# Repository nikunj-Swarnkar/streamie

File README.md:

### streamie

---

a hackpad or a streaming device with a gamepad in which you can stream your games or play some retro games natively , hack it , add a keyboard and sky is your limit , it runs android !

---

## Cad 

this is the case i prepared 

## PCB

---

## Flashing
for the Raxda please follow raxda offical guide , please flash it before assembly 
[Raxda Site](https://docs.radxa.com/en/cubie/a7z/other-system/android)

The controller runs on an RP2040-Zero and flashes by drag-and-drop. No programmer is needed.

### Option 1: flash a prebuilt file
1. Download `controller_xinput.uf2` from the Releases page.
2. Unplug the board from USB.
3. Hold the **BOOT** button and plug the board into your computer. Release BOOT once it's connected.
4. A drive named **RPI-RP2** appears. Drag `controller_xinput.uf2` onto it.
5. The drive disappears and the board restarts as a controller.

### Option 2: build it yourself
Requirements: [VS Code](https://code.visualstudio.com/) with the **Raspberry Pi Pico** extension. It installs the Pico SDK (2.x), compiler and CMake for you.

1. Clone this repo and open the `firmware/xinput` folder in VS Code (**File > Open Folder**). It must be the folder that directly contains `CMakeLists.txt`.
2. In the Pico extension, choose **Import Project** and select that folder.
3. Check that `CMakeLists.txt` has `set(PICO_BOARD waveshare_rp2040_zero)`. Use `pico` if you have a regular Raspberry Pi Pico.
4. Click **Compile Project**. The result is `build/controller_xinput.uf2`.
5. Flash it with the steps from Option 1.

If you use the command line instead, run:
```
mkdir build && cd build
cmake -DPICO_SDK_PATH=/path/to/pico-sdk ..
cmake --build .
```

### Verify it works
1. Keep the **sticks centered and the triggers released** when you plug it in, because they are calibrated at power-up.
2. On Windows, press **Win + R**, type `joy.cpl` and press Enter. The board should appear as **Xbox 360 Controller**.
3. Open **Properties** and check every button, both sticks and both triggers.
4. Pull each trigger fully once so it learns its travel.

### Settings in `main.c`
| Setting | What it does |
|---|---|
| `INVERT_LY`, `INVERT_RY` | Set to `true` if a stick's up and down are backwards |
| `STICK_DEADZONE` | Raise it if the sticks drift |
| `R3_PRESSED_BELOW` | Threshold for the right stick click, which is read through the MCP3008 (CH6) |

### Updating the firmware
Repeat the flashing steps. Always hold **BOOT** while plugging in, even if the board is already running this firmware.

### Troubleshooting
- **No RPI-RP2 drive:** try a different USB cable, because many cables carry power only. Make sure you hold BOOT *before* plugging in.
- **Not recognised as an Xbox controller:** check Device Manager for an unknown device, and try a different USB port.
- **Triggers read constant or backwards:** check the trigger pot wiring. The wiper (middle pad) must go to the MCP3008 channel.
- **Stick axes backwards:** flip `INVERT_LY` or `INVERT_RY` and re-flash.
- **No rumble:** it works only in games and testers that send XInput rumble. Check that the motor MOSFET gates are wired to GP26 and GP27.
- **Compile fails in VS Code:** make sure the open folder is the one containing `CMakeLists.txt`, then run **Clean CMake** and **Compile Project** again.

Compatibility: Windows and Linux. Consoles will not accept this controller.

---

## Assembly 

after printing the case add screen on in it 

then add the front latch to the screen and secure it with 4 M3 screws 

after that add all the buttons from the back 

then put the pcb on it 

and then rest of the parts and add aux post connected to the screen and add a A7z with stand off and wire everything 

connect the controller through usb cable after connecting both side with jst connector , then wire the tp4056 with buck convertor and make sure to set it at 5 v 

after that add the battery to the back and stick it to the back indent with m3 tape or doulbe side tape

after that then just wire it to the tp4056 
and the buckconvertor to the 5v n gnd of the Raxda A7z connect the display with hdmi and if u want touch a usb cable 

after all that 

just screw in the last 4 M3 screws 

and we are done ! 

---

# Bill of Materials (BOM)

| Sr. No. | Name | Link | Unit Price (USD) | Quantity | Total Price (USD) |
|---:|---|---|---:|---:|---:|
| 1 | JST male | [Product link](https://sharvielectronics.com/product/ph-14aw-14-pin-jst-right-angle-male-connector-2mm-pitch/) | 0.130 | 6 | 0.780 |
| 2 | JST female | [Product link](https://sharvielectronics.com/product/jst-ph-14-14-pin-single-side-female-to-free-end-connector-with-2mm-pitch-30cm-wire-length/) | 0.510 | 6 | 3.060 |
| 3 | 90-degree push button | [Product link](https://sharvielectronics.com/product/push-button-right-angle-tactile-switch-6x5mm-right-angle-tactile-switch-momentary-switch/) | 0.710 | 10 | 7.100 |
| 4 | Joystick | [Product link](https://sharvielectronics.com/product/thumb-joystick-switch-xy-dual-axis-4-way-direction/) | 0.660 | 4 | 2.640 |
| 5 | Screen | [Product link](https://makerbazar.in/products/waveshare-5-inch-capacitive-hdmi-lcd-display-h-800-480?variant=43342621311216) | 51.670 | 1 | 51.670 |
| 6 | Battery | [Product link](https://makerbazar.in/products/single-cell-3-7v-10000mah-lipo-battery?variant=48251044659440) | 4.120 | 1 | 4.120 |
| 7 | Buck converter (listed as XL6009) | [Product link](https://makerbazar.in/products/xl6009-dc-dc-adjustable-boost-buck-step-up-step-down-converter-module) | 0.670 | 1 | 0.670 |
| 8 | SMD push button | [Product link](https://makerbazar.in/products/5-2x5-2mm-smd-copper-push-button-tactile-switch?variant=48101517852912) | 0.200 | 2 | 0.400 |
| 9 | Vibration motor | [Product link](https://makerbazar.in/products/coin-type-micro-disc-vibration-motor?variant=48251066024176) | 0.200 | 4 | 0.800 |
| 10 | MCP3008 ADC | [Product link](https://sharvielectronics.com/product/mcp3008-i-p-8-channel-10-bit-adc-with-spi-interface-ic-dip-16-package/) | 3.530 | 1 | 3.530 |
| 11 | 1N4739A Zener diode (9.1 V) | [Product link](https://sharvielectronics.com/product/1n4739a-9-1v-1watt-zener-diode-%c2%b15-tolerance-do-41-package/) | 0.034 | 4 | 0.136 |
| 12 | Waveshare RP2040 Zero | [Product link](https://sharvielectronics.com/product/waveshare-rp2040-zero-without-header/) | 3.800 | 1 | 3.800 |
| 13 | AO3400 MOSFET | [Product link](https://sharvielectronics.com/product/ao3400-30v-5-8a-n-channel-mosfet-sot-23-package/) | 0.100 | 5 | 0.500 |
| 14 | RK09K1110A0J | [Product link](https://robu.in/product/1-month-warranty-1035/) | 0.580 | 2 | 1.160 |
| 15 | 10 kΩ resistor | [Product link](https://sharvielectronics.com/product/10k-ohm-1-watt-metal-film-resistor-1-tolerance/) | 0.920 | 10 | 9.200 |
| 16 | 100 Ω resistor | [Product link](https://sharvielectronics.com/product/100-ohm-1-2-watt-resistor-5-tolerance/) | 0.012 | 10 | 0.120 |
| 17 | 100 kΩ resistor | [Product link](https://sharvielectronics.com/product/100k-ohm-2-watt-metal-film-resistor-1-tolerance/) | 0.095 | 10 | 0.950 |
| 18 | Radxa Cubie A7Z | [Product link](https://evelta.com/cubie-a7z-tiny-size-mighty-ai-sbc-radxa/) | 62.120 | 1 | 62.120 |
| 19 | AUX port/cable | [Product link](https://sharvielectronics.com/product/3-5mm-aux-male-to-female-audio-extension-cable-1-meter/) | 1.020 | 1 | 1.020 |
| 20 | Micro-HDMI to HDMI cable/adapter | [Product link](https://sharvielectronics.com/product/micro-hdmi-male-to-hdmi-male-adapter/) | 1.540 | 1 | 1.540 |
| 21 | USB-C to USB-C cable | [Product link](https://www.amazon.in/Wayona-Powerbank-charging-compatible-Samsung/dp/B08WKJN4LF?source=ps-sl-shoppingads-lpcontext&smid=A2V43CXDBM3YTI&th=1) | 3.030 | 1 | 3.030 |
|  | **Grand Total** |  |  |  | **158.346** |

---

and we are done , ill update the github now when i make the project ~

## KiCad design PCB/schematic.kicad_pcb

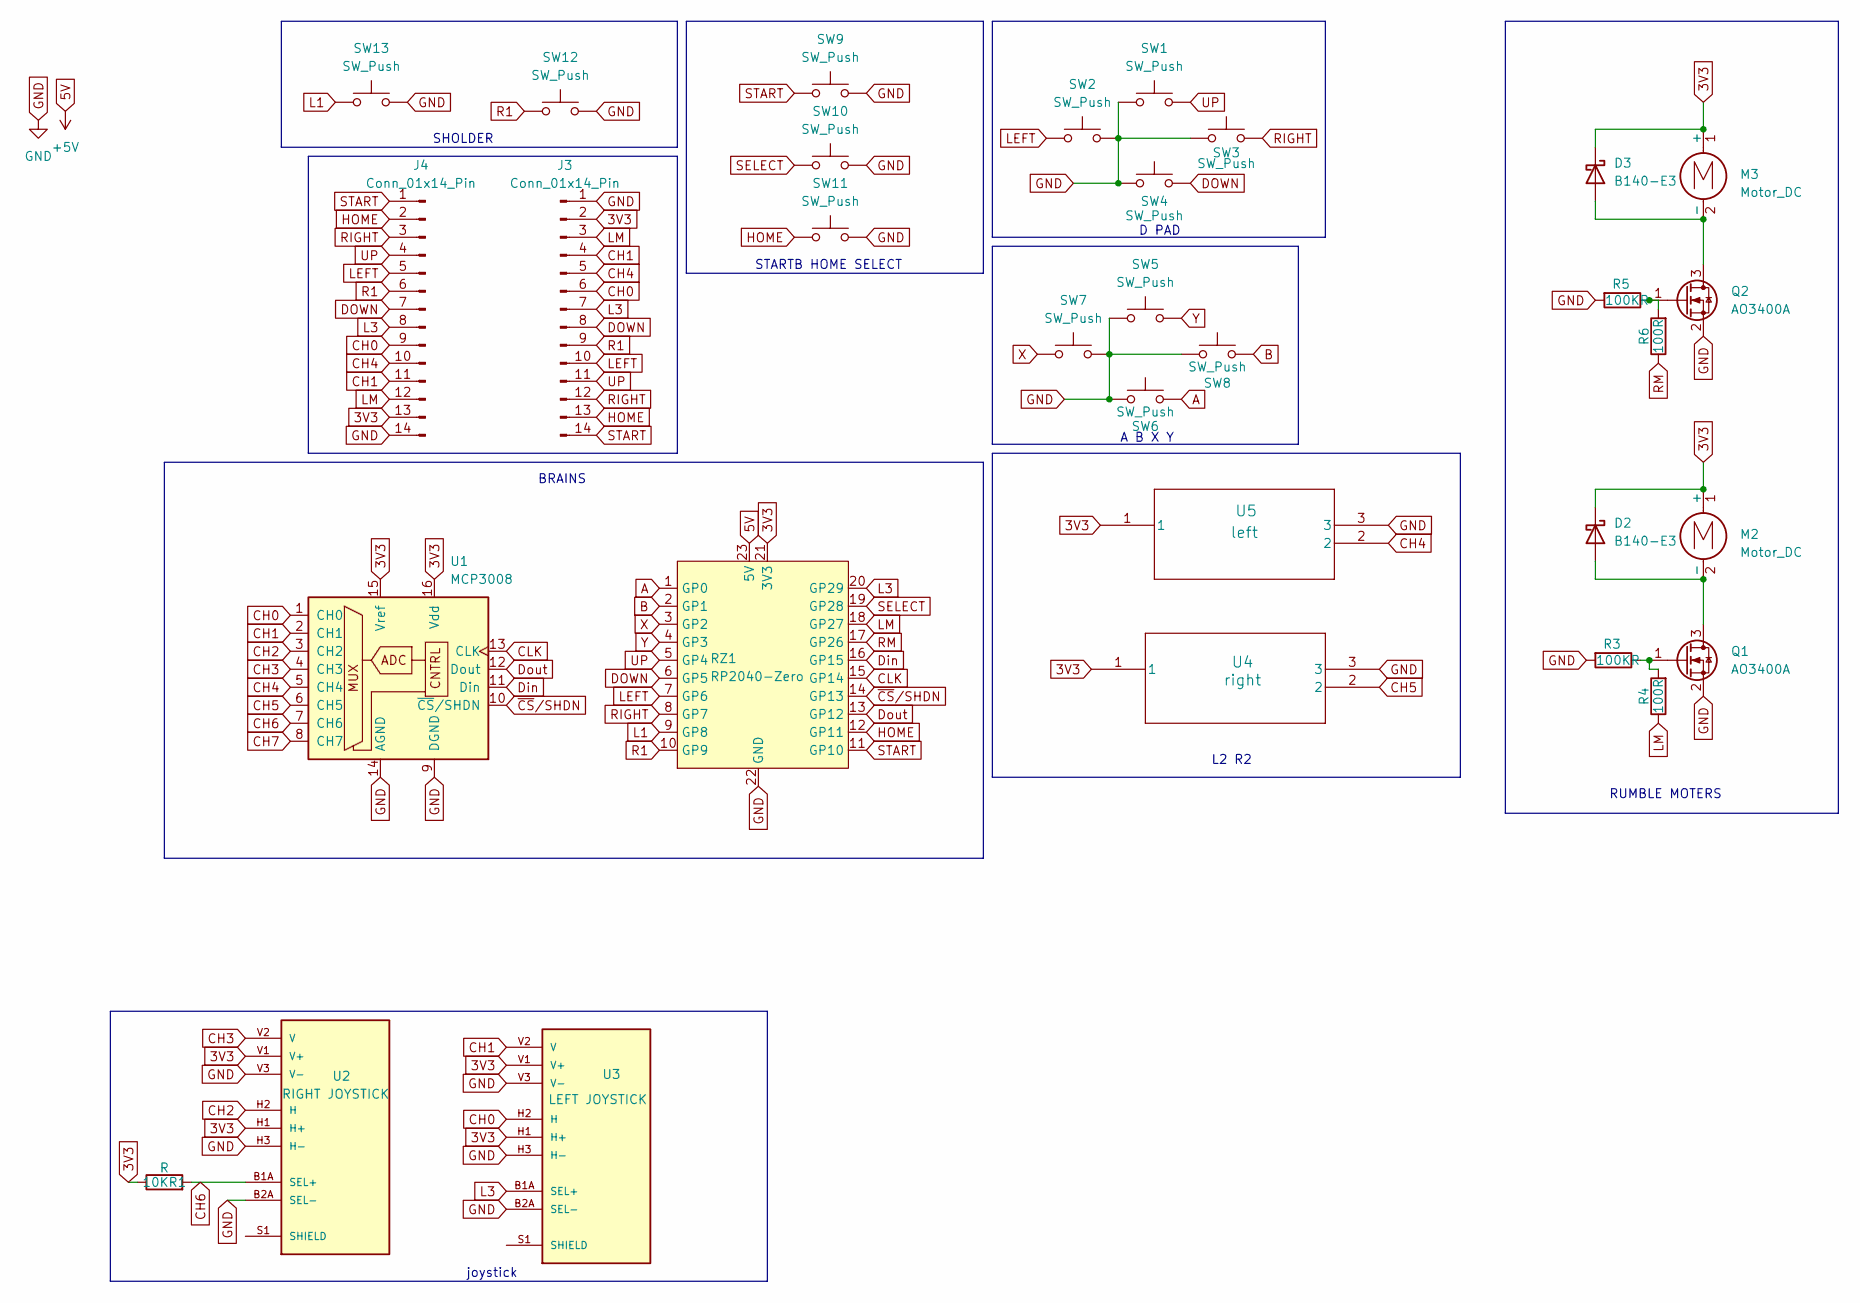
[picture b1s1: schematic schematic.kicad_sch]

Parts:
10KR1: R; R_Axial_DIN0207_L6.3mm_D2.5mm_P7.62mm_Horizontal
D2, D3: B140-E3; D_SMA
J3, J4: Conn_01x14_Pin; JST_PH_S14B-PH-K_1x14_P2.00mm_Horizontal
M2, M3: Motor_DC; MOTOR_2PAD
Q1, Q2: AO3400A; SOT-23
R3, R5: 100KR; R_Axial_DIN0207_L6.3mm_D2.5mm_P7.62mm_Horizontal
R4, R6: 100R; R_Axial_DIN0207_L6.3mm_D2.5mm_P7.62mm_Horizontal
RZ1: RP2040-Zero; MODULE_RP2040-ZERO
SW1, SW2, SW3, SW4, SW5, SW6, SW7, SW8, SW9, SW10, SW11: SW_Push; SW_5.2x5.2x2.0
SW12, SW13: SW_Push; SW_Tactile_SPST_Angled_PTS645Vx58-2LFS
U1: MCP3008; DIP-16_W7.62mm_LongPads
U2: RIGHT JOYSTICK; XDCR_COM-09032; PARTREV N/A
U3: LEFT JOYSTICK; XDCR_COM-09032; PARTREV N/A
U4: right; Potentiometer_Alps_RK09K_Single_Horizontal
U5: left; Potentiometer_Alps_RK09K_Single_Horizontal

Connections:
3V3: 10KR1.1, D2.1 (K), D3.1 (K), J3.2, J4.13, M2.1 (+), M3.1 (+), RZ1.21 (3V3), U1.15 (Vref), U1.16 (Vdd), U2.H1 (H+), U2.V1 (V+), U3.H1 (H+), U3.V1 (V+), U4.1, U5.1
5V: RZ1.23 (5V)
A: RZ1.1 (GP0), SW6.2
B: RZ1.2 (GP1), SW8.2
CH0: J3.6, J4.9, U1.1 (CH0), U3.H2 (H)
CH1: J3.4, J4.11, U1.2 (CH1), U3.V2 (V)
CH2: U1.3 (CH2), U2.H2 (H)
CH3: U1.4 (CH3), U2.V2 (V)
CH4: J3.5, J4.10, U1.5 (CH4), U5.2
CH5: U1.6 (CH5), U4.2
CH6: 10KR1.2, U1.7 (CH6), U2.B1A (SEL+)
CH7: U1.8 (CH7)
CLK: RZ1.15 (GP14), U1.13 (CLK)
DOWN: J3.8, J4.7, RZ1.6 (GP5), SW4.2
Din: RZ1.16 (GP15), U1.11 (Din)
Dout: RZ1.13 (GP12), U1.12 (Dout)
GND: J3.1, J4.14, Q1.2 (S), Q2.2 (S), R3.2, R5.2, RZ1.22 (GND), SW1.1, SW2.2, SW3.1, SW4.1, SW5.1, SW6.1, SW7.2, SW8.1, SW9.2, SW10.2, SW11.2, SW12.2, SW13.2, U1.9 (DGND), U1.14 (AGND), U2.B2A (SEL-), U2.H3 (H-), U2.V3 (V-), U3.B2A (SEL-), U3.H3 (H-), U3.V3 (V-), U4.3, U5.3
HOME: J3.13, J4.2, RZ1.12 (GP11), SW11.1
L1: RZ1.9 (GP8), SW13.1
L3: J3.7, J4.8, RZ1.20 (GP29), U3.B1A (SEL+)
LEFT: J3.10, J4.5, RZ1.7 (GP6), SW2.1
LM: J3.3, J4.12, R4.1, RZ1.18 (GP27)
unnamed: D2.2 (A), M2.2 (-), Q1.3 (D)
unnamed: D3.2 (A), M3.2 (-), Q2.3 (D)
unnamed: Q1.1 (G), R3.1, R4.2
unnamed: Q2.1 (G), R5.1, R6.2
unnamed: U2.S1 (SHIELD), U2.S2 (SHIELD), U2.S3 (SHIELD), U2.S4 (SHIELD)
unnamed: U3.S1 (SHIELD), U3.S2 (SHIELD), U3.S3 (SHIELD), U3.S4 (SHIELD)
R1: J3.9, J4.6, RZ1.10 (GP9), SW12.1
RIGHT: J3.12, J4.3, RZ1.8 (GP7), SW3.2
RM: R6.1, RZ1.17 (GP26)
SELECT: RZ1.19 (GP28), SW10.1
START: J3.14, J4.1, RZ1.11 (GP10), SW9.1
UP: J3.11, J4.4, RZ1.5 (GP4), SW1.2
X: RZ1.3 (GP2), SW7.1
Y: RZ1.4 (GP3), SW5.2

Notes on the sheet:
STARTB HOME SELECT
A B X Y
D PAD
L2 R2
joystick
RUMBLE MOTERS
BRAINS
SHOLDER

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
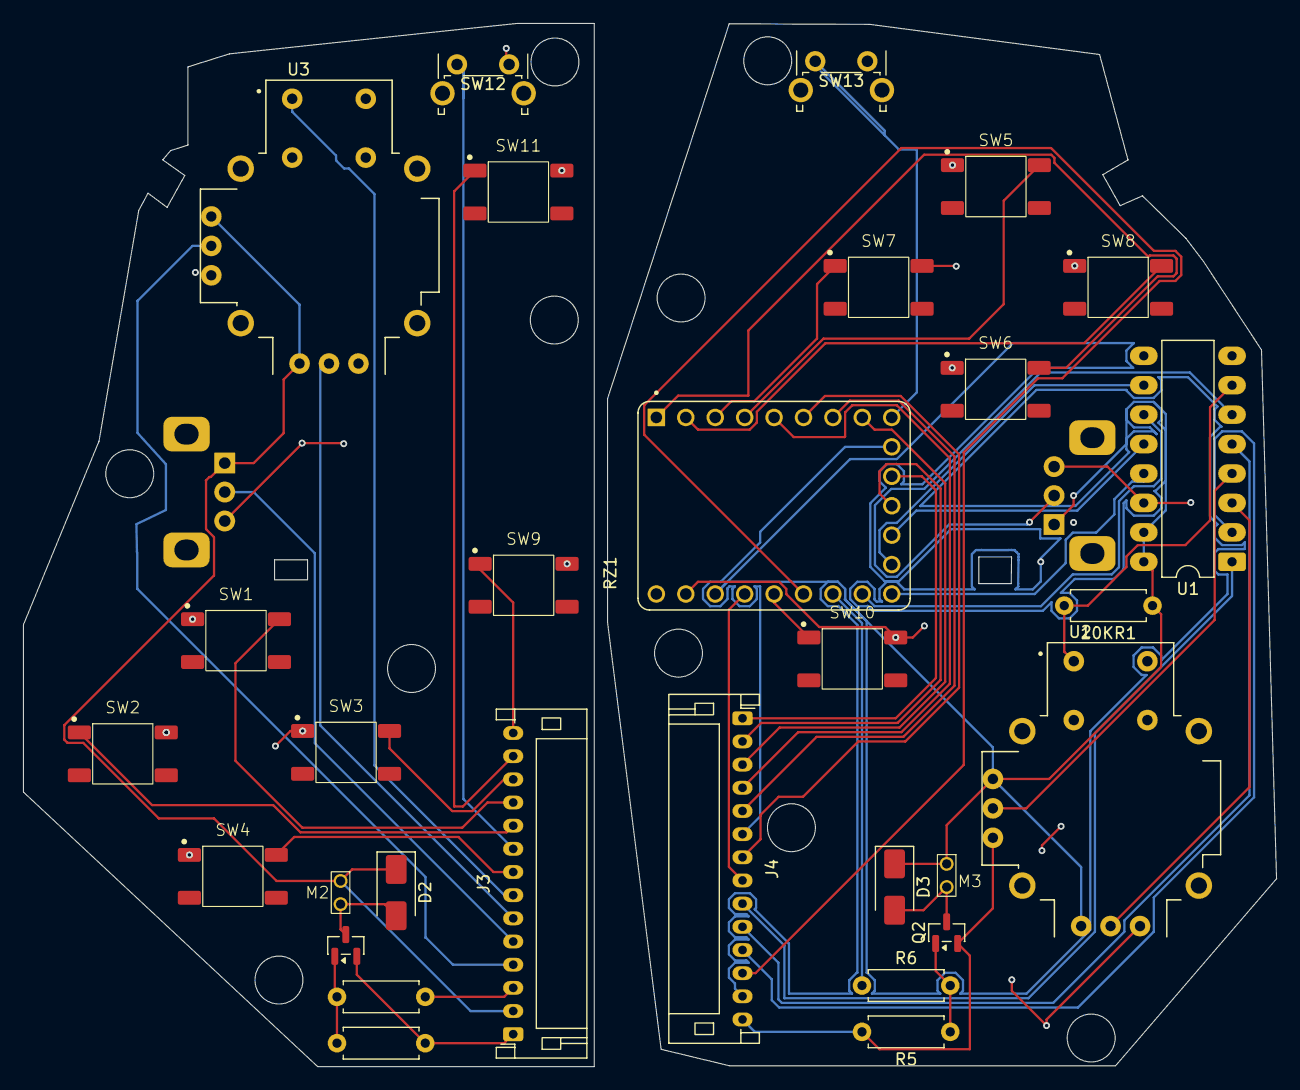
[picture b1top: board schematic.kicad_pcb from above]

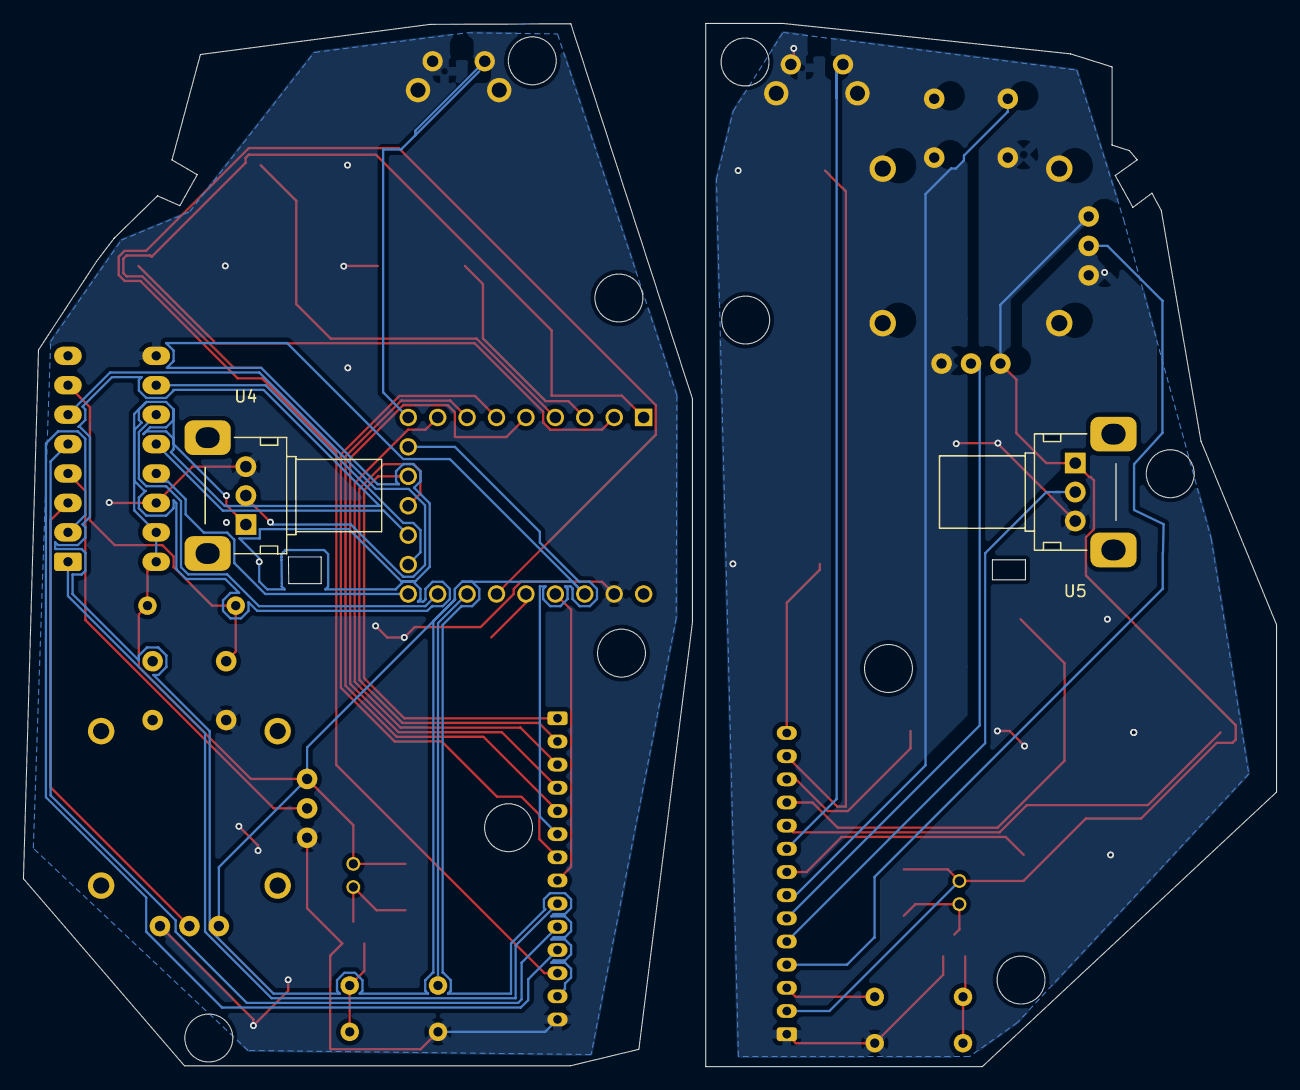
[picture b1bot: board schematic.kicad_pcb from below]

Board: 2 copper layers, 108.2 x 90.1 mm, 32 parts (2 on the bottom side), 35 nets.
